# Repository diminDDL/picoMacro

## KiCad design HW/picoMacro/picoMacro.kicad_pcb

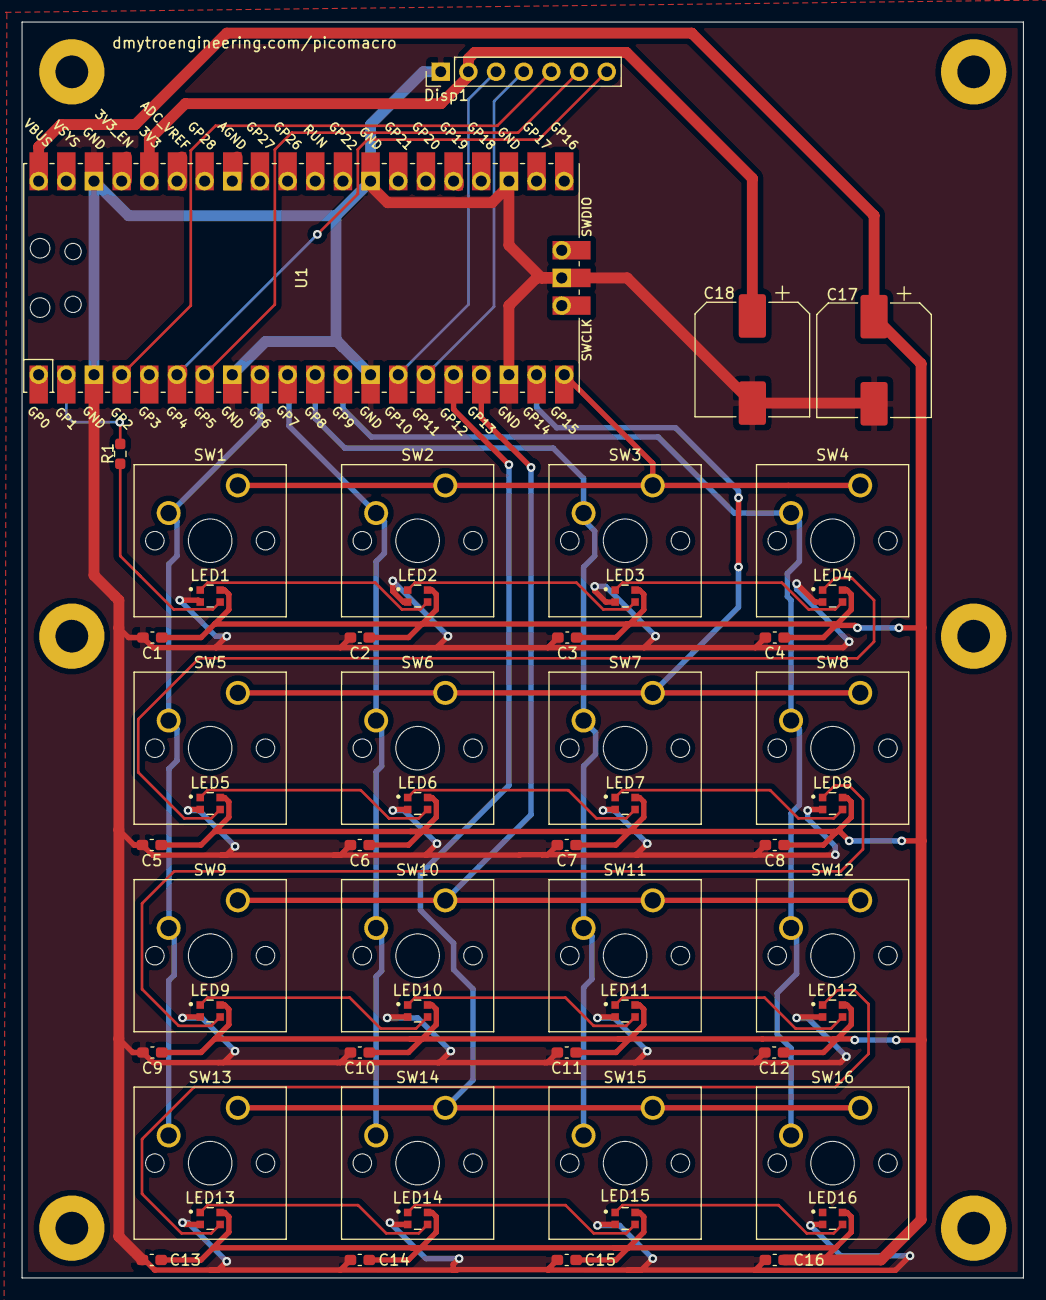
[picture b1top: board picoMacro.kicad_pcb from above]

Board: 2 copper layers, 91.9 x 115.3 mm, 53 parts (0 on the bottom side), 33 nets.

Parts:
C1, C2, C3, C4, C5, C6, C7, C8, C9, C10, C11, C12, C13, C14, C15, C16: 100n; C_0603_1608Metric_Pad1.08x0.95mm_HandSolder
C17: 470u; CP_Elec_10x10
C18: 100u; CP_Elec_10x10
Disp1: 1.3_OLED_SH1106; PinHeader_1x07_P2.54mm_Vertical
LED1, LED2, LED3, LED4, LED5, LED6, LED7, LED8, LED9, LED10, LED11, LED12, LED13, LED14, LED15, LED16: WS2812-2020; LED_WS2812-2020
R1: 470; R_0603_1608Metric_Pad0.98x0.95mm_HandSolder
SW1, SW2, SW3, SW4, SW5, SW6, SW7, SW8, SW9, SW10, SW11, SW12, SW13, SW14, SW15, SW16: SW_Push; SW_Cherry_MX_1.00u_PCB
U1: Pico; RPi_Pico_SMD_TH

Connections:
+3V3: C18.1, Disp1.2, U1.36
+5V: C1.1, C2.1, C3.1, C4.1, C5.1, C6.1, C7.1, C8.1, C9.1, C10.1, C11.1, C12.1, C13.1, C14.1, C15.1, C16.1, C17.1, LED1.4, LED2.4, LED3.4, LED4.4, LED5.4, LED6.4, LED7.4, LED8.4, LED9.4, LED10.4, LED11.4, LED12.4, LED13.4, LED14.4, LED15.4, LED16.4, U1.40
GND: C1.2, C2.2, C3.2, C4.2, C5.2, C6.2, C7.2, C8.2, C9.2, C10.2, C11.2, C12.2, C13.2, C14.2, C15.2, C16.2, C17.2, C18.2, Disp1.1, LED1.2, LED2.2, LED3.2, LED4.2, LED5.2, LED6.2, LED7.2, LED8.2, LED9.2, LED10.2, LED11.2, LED12.2, LED13.2, LED14.2, LED15.2, LED16.2, U1.3, U1.8, U1.13, U1.18, U1.23, U1.28, U1.38, U1.42
unnamed: Disp1.3, U1.14
unnamed: Disp1.4, U1.15
unnamed: Disp1.5, U1.4
unnamed: Disp1.6, U1.7
unnamed: Disp1.7, U1.6
unnamed: LED1.1, LED2.3
unnamed: LED1.3, R1.1
unnamed: LED2.1, LED3.3
unnamed: LED3.1, LED4.3
unnamed: LED4.1, LED5.3
unnamed: LED5.1, LED6.3
unnamed: LED6.1, LED7.3
unnamed: LED7.1, LED8.3
unnamed: LED8.1, LED9.3
unnamed: LED10.1, LED11.3
unnamed: LED9.1, LED10.3
unnamed: LED11.1, LED12.3
unnamed: LED12.1, LED13.3
unnamed: LED13.1, LED14.3
unnamed: LED14.1, LED15.3
unnamed: LED15.1, LED16.3
unnamed: R1.2, U1.2
unnamed: SW1.1, SW2.1, SW3.1, SW4.1, U1.20
unnamed: SW1.2, SW5.2, SW9.2, SW13.2, U1.9
unnamed: SW5.1, SW6.1, SW7.1, SW8.1, U1.19
unnamed: SW9.1, SW10.1, SW11.1, SW12.1, U1.17
unnamed: SW2.2, SW6.2, SW10.2, SW14.2, U1.10
unnamed: SW3.2, SW7.2, SW11.2, SW15.2, U1.11
unnamed: SW4.2, SW8.2, SW12.2, SW16.2, U1.12
unnamed: SW13.1, SW14.1, SW15.1, SW16.1, U1.16

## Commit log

2021-09-06 add existing proof of concept
2021-09-06 added shortcut label to main.py
2021-10-28 button customixation menu is now in proper location
2022-05-12 added C sdk project
2022-05-12 added gitignore to the build folder
2022-05-12 added cmakelist.txt
2022-05-18 added hardware
2022-05-18 ws2812 via PIO working
2022-05-18 added build script
2022-05-18 fixed the build script
2022-05-19 moved WS2812 code in to a separate file for less clutter
2022-05-19 usb HID functionality added
2022-05-20 added description of the key shortcut storage method
2022-05-21 updated the WSLED methods, moved init inside the libs
2022-05-22 testing USB HID + printf
2022-05-22 removed old non working code
2022-05-22 removed a file from the wrong location
2022-05-25 USB HID + printf working, hard coded directory for now
2022-05-26 proof of concept macropad working
2022-05-28 converted to cpp for future OOP usage
2022-05-31 added key storage class
2022-05-31 messing with the key class more
2022-06-03 basic class functions working
2022-06-04 fixed bug with reporting method
2022-06-04 fixed a bug where same key will not be reported second time
2022-06-04 fixed some timings bugs but stil needs work
2022-06-06 proof of concept preiodic calling working
2022-06-06 set up on chip debugger
2022-07-13 fixed build in 1.4.0 sdk
2025-02-17 minor updates
